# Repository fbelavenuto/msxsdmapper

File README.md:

# Projeto descontinuado
### Nova versão em https://github.com/fbelavenuto/msxsdmapperv2

## MSX SDMapper
Projeto SD Mapper/Megaram 512K para MSX

Copyright (c) 2014 Fabio Belavenuto. Licenced under CERN OHL v1.1

This documentation describes Open Hardware and is licensed under the CERN OHL v. 1.1.
You may redistribute and modify this documentation under the terms of the
[CERN OHL v.1.1](http://ohwr.org/cernohl). This documentation is distributed
WITHOUT ANY EXPRESS OR IMPLIED WARRANTY, INCLUDING OF MERCHANTABILITY,
SATISFACTORY QUALITY AND FITNESS FOR A PARTICULAR PURPOSE.
Please see the CERN OHL v.1.1 for applicable conditions

Este projeto implementa uma interface em forma de cartucho para adicionar um
dispositivo de armazenamento em massa utilizando até dois cartões SD (Secure
Digital) e uma Mapper ou Megaram de 512K para computadores da linha MSX.

O cartão SD pode ser padrão SD ou SDHC, o que limita o tamanho em no máximo
32GB.

Foi utilizado como sistema operacional o [Nextor](http://www.konamiman.com/msx/msx-e.html#nextor) sendo desenvolvido somente
o driver para se ter acesso aos dois cartões SD. O Nextor agora se tornou um projeto aberto em 2018.

O Nextor é uma evolução do MSX-DOS 2 tendo nativamente suporte a partições FAT16
de até 4GB, podendo ter 4 partições por cartão SD. Isso limita o máximo de uso do cartão SD em 16GB. É necessário 128KB de Mapper no mínimo para utilizar o Nextor com acesso à sub-diretórios, menos que 128K de mapper permite somente o uso do kernel do MSXDOS1 limitando em partições com FAT12 e máximo de 16MB por partição.

Uma chave seleciona entre os modos Mapper ou Megaram. A Megaram é um projeto do Ademir Carchano e permite executar ROMs de jogos/programas de cartuchos Megarom.

A função Mapper/Megaram pode ser desativada por uma outra chave e é útil no caso de usar a interface em um MSX que já tenha Mapper e não quiser usar a Megaram.

Foi criado um utilitário chamado "sdmupd.com" para poder atualizar a flash pelo próprio MSX.

Para compilar o driver e o utilitário sdmupd.com utilize o montador do próprio criador do Nextor [Nestor80](https://github.com/Konamiman/Nestor80) e para compilar o código do CPLD utilize o [Xilinx ISE Webpack](https://www.xilinx.com/support/download/index.html/content/xilinx/en/downloadNav/vivado-design-tools/archive-ise.html).

Agradecimentos ao Ademir Carchano pela invenção da Megaram, ao Luciano Sturaro pelo roteamento da placa e a comunidade MSXBR-L pelo apoio e incentivo.

#### Detalhes técnicos:

  - O código do CPLD implementa toda a lógica necessária, implementando um expansor
    de slots padrão, uma porta SPI modo 0, o controle da MegaROM padrão ASCII16
    utilizada pelo Nextor e o controle da Mapper ou Megaram de 512K.
  - Ao ativar a mapper/megaram, a interface ativa o expansor de slots, e com isso a
    interface funciona somente em slots não-expandidos. Porém, se desativar a
    mapper/megaram, o expansor de slots é desativado, permitindo utilizar o
    dispositivo de armazenamento em massa em slots expandidos.
  - A porta SPI implementada utiliza mapa de memória de $4000 a $48FF, sendo o 
    chaveamento entre ROM e SPI configurado pela escrita no endereço $6001.
  - Foi previsto a atualização da memória flash por software. Para isto foi
    implementado a porta 0x5F que controla a ativação ou não da gravação da flash.
    O bit 7 controla a permissão de gravação e os bits 2, 1 e 0 controlam a paginação
    de 16KB. Ao ativar o bit 7 a flash é mapeada em qualquer página (repete o mesmo
    espaço de 16K nas 4 páginas) e os bits 2, 1 e 0 controlam qual das 8 páginas da
    flash será mapeada. O sinal /WR da flash só é gerado quando o bit 7 está ativo.
    O utilitário sdmupd.com utiliza esta porta para poder atualizar a flash pelo
    próprio MSX.

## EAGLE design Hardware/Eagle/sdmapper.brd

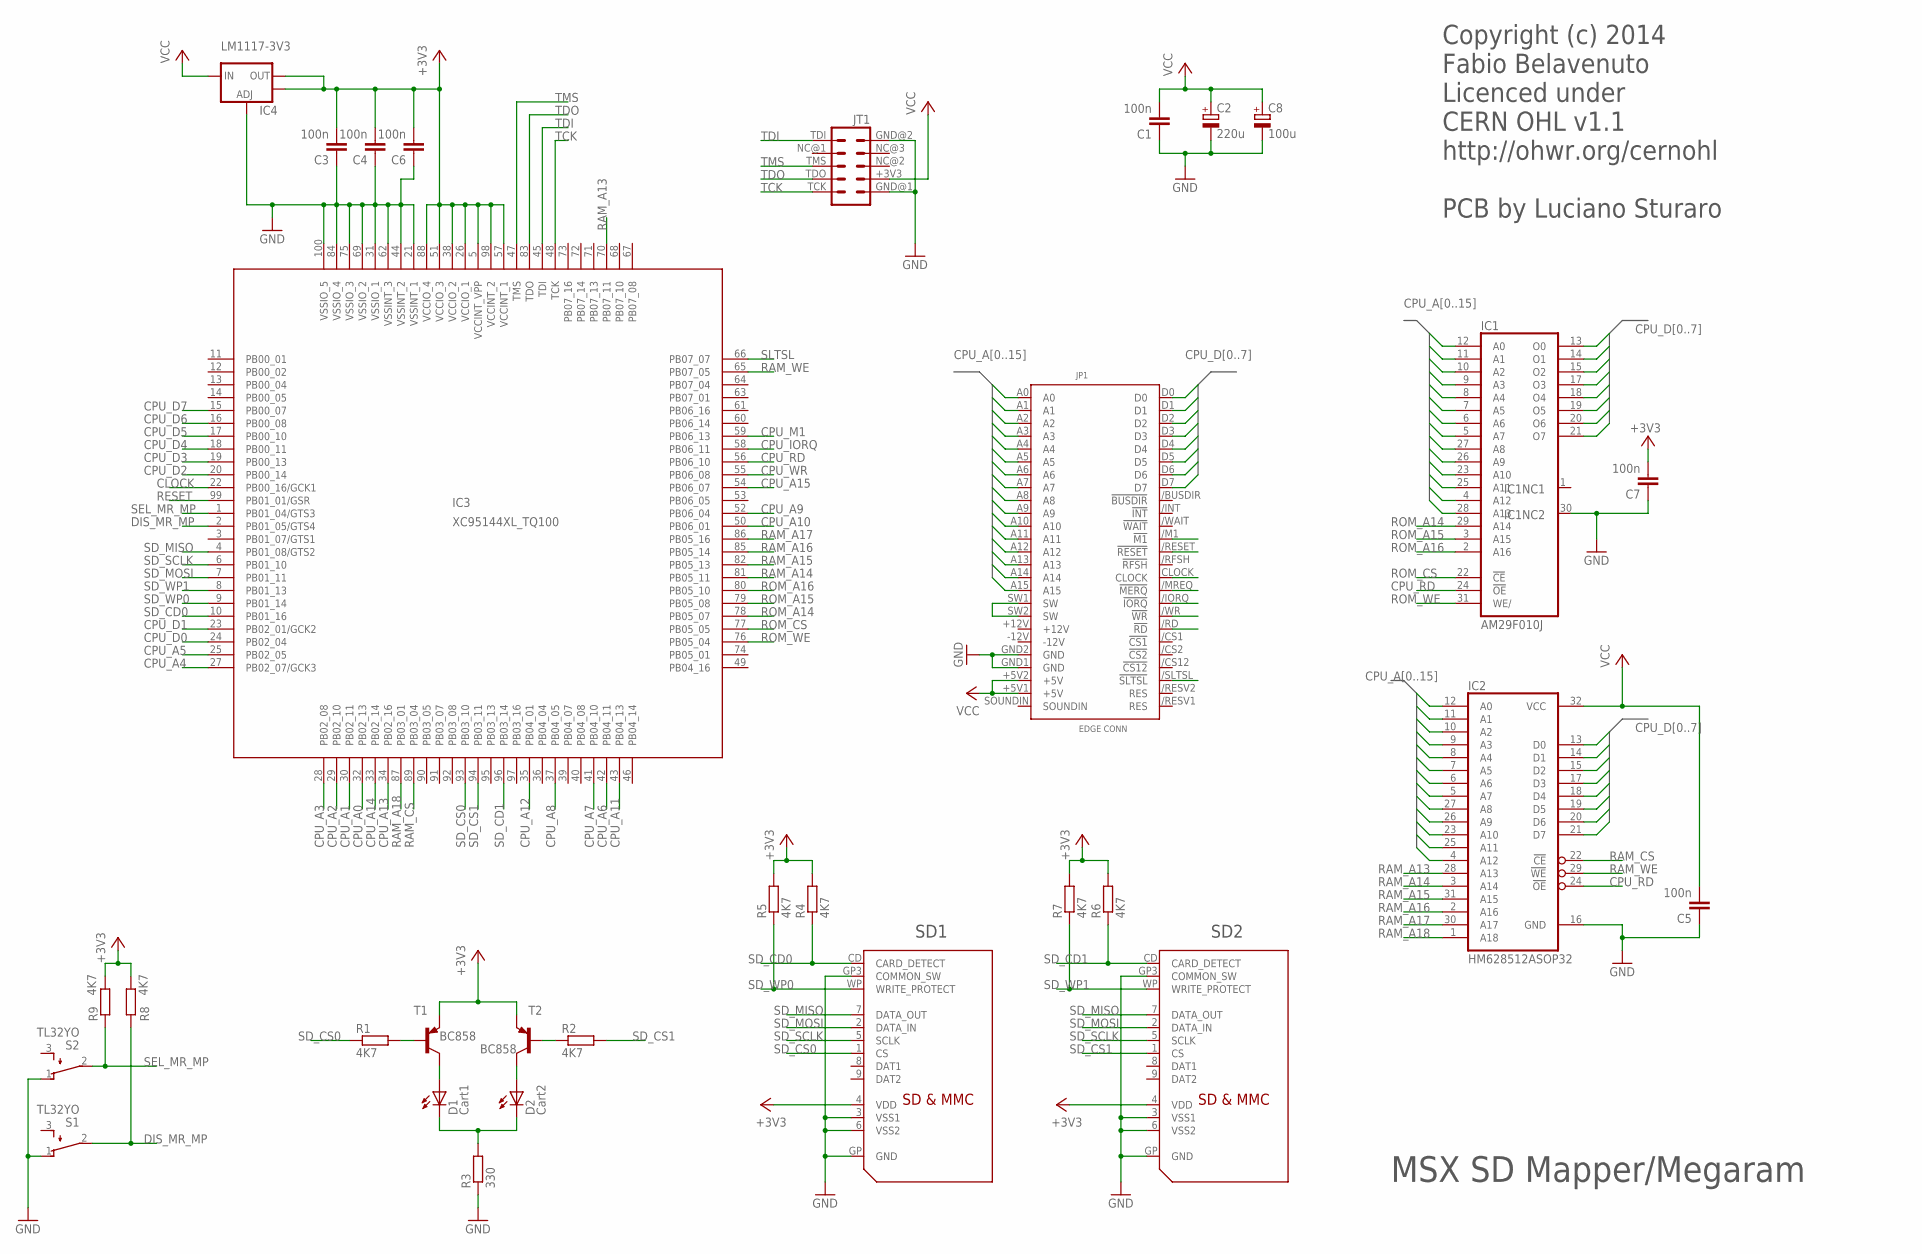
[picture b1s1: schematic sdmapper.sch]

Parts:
C1, C3, C4, C5: 100n; C0805
C2: 220u; E3,5-8
C6, C7: 100n; C1206
C8: 100u; PANASONIC_C
D1: Cart1; LED3MM
D2: Cart2; LED3MM
IC1: AM29F010J; PLCC32R
IC2: HM628512ASOP32; SOP32
IC3: XC95144XL_TQ100; XC-TQ100
IC4: LM1117-3V3; SOT223
JP1: MSXCART1; MSXCART
JT1: JTAG1B; SMD5X2
R1, R2, R4, R5, R6, R7, R8, R9: 4K7; R0805
R3: 330; R0805
S1, S2: TL32YO; TL3XYO
SD1, SD2: SDMMC06132; 06132
T1, T2: BC858; SOT23-BEC

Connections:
+3V3: C3.2, C4.2, C6.2, C7.2, IC3.5 (VCCINT_VPP), IC3.26 (VCCIO_1), IC3.38 (VCCIO_2), IC3.51 (VCCIO_3), IC3.57 (VCCINT_1), IC3.88 (VCCIO_4), IC3.98 (VCCINT_2), IC4.2 (OUT), IC4.4 (OUT), R4.2, R5.2, R6.2, R7.2, R8.2, R9.2, SD1.4 (VDD), SD2.4 (VDD), T1.E, T2.E
CLOCK: IC3.22 (PB00_16/GCK1), JP1.CLOCK
CPU_A0: IC1.12 (A0), IC2.12 (A0), IC3.32 (PB02_13), JP1.A0
CPU_A1: IC1.11 (A1), IC2.11 (A1), IC3.30 (PB02_11), JP1.A1
CPU_A2: IC1.10 (A2), IC2.10 (A2), IC3.29 (PB02_10), JP1.A2
CPU_A3: IC1.9 (A3), IC2.9 (A3), IC3.28 (PB02_08), JP1.A3
CPU_A4: IC1.8 (A4), IC2.8 (A4), IC3.27 (PB02_07/GCK3), JP1.A4
CPU_A5: IC1.7 (A5), IC2.7 (A5), IC3.25 (PB02_05), JP1.A5
CPU_A6: IC1.6 (A6), IC2.6 (A6), IC3.42 (PB04_11), JP1.A6
CPU_A7: IC1.5 (A7), IC2.5 (A7), IC3.41 (PB04_10), JP1.A7
CPU_A8: IC1.27 (A8), IC2.27 (A8), IC3.37 (PB04_05), JP1.A8
CPU_A9: IC1.26 (A9), IC2.26 (A9), IC3.52 (PB06_04), JP1.A9
CPU_A10: IC1.23 (A10), IC2.23 (A10), IC3.50 (PB06_01), JP1.A10
CPU_A11: IC1.25 (A11), IC2.25 (A11), IC3.43 (PB04_13), JP1.A11
CPU_A12: IC1.4 (A12), IC2.4 (A12), IC3.35 (PB04_01), JP1.A12
CPU_A13: IC1.28 (A13), IC3.34 (PB02_16), JP1.A13
CPU_A14: IC3.33 (PB02_14), JP1.A14
CPU_A15: IC3.54 (PB06_07), JP1.A15
CPU_D0: IC1.13 (O0), IC2.13 (D0), IC3.24 (PB02_04), JP1.D0
CPU_D1: IC1.14 (O1), IC2.14 (D1), IC3.23 (PB02_01/GCK2), JP1.D1
CPU_D2: IC1.15 (O2), IC2.15 (D2), IC3.20 (PB00_14), JP1.D2
CPU_D3: IC1.17 (O3), IC2.17 (D3), IC3.19 (PB00_13), JP1.D3
CPU_D4: IC1.18 (O4), IC2.18 (D4), IC3.18 (PB00_11), JP1.D4
CPU_D5: IC1.19 (O5), IC2.19 (D5), IC3.17 (PB00_10), JP1.D5
CPU_D6: IC1.20 (O6), IC2.20 (D6), IC3.16 (PB00_08), JP1.D6
CPU_D7: IC1.21 (O7), IC2.21 (D7), IC3.15 (PB00_07), JP1.D7
CPU_IORQ: IC3.58 (PB06_11), JP1./IORQ (!IORQ)
CPU_M1: IC3.59 (PB06_13), JP1./M1 (!M1)
CPU_MREQ: JP1./MREQ (!MERQ)
CPU_RD: IC1.24 (!OE), IC2.24 (!OE), IC3.56 (PB06_10), JP1./RD (!RD)
CPU_WR: IC3.55 (PB06_08), JP1./WR (!WR)
DIS_MR_MP: IC3.2 (PB01_05/GTS4), R8.1, S1.2
GND: C1.1, C2.-, C3.1, C4.1, C5.1, C6.1, C7.1, C8.-, IC1.16 (GND), IC1.30 (NC), IC2.16 (GND), IC3.21 (VSSINT_1), IC3.31 (VSSIO_1), IC3.44 (VSSINT_2), IC3.62 (VSSINT_3), IC3.69 (VSSIO_2), IC3.75 (VSSIO_3), IC3.84 (VSSIO_4), IC3.100 (VSSIO_5), IC4.1 (ADJ), JP1.GND1 (GND), JP1.GND2 (GND), JT1.GND@1 (TDI), JT1.GND@2 (TCK), R3.1, S1.1 (O), S2.1 (O), SD1.3 (VSS1), SD1.6 (VSS2), SD1.GP (GND), SD1.GP3 (COMMON_SW), SD2.3 (VSS1), SD2.6 (VSS2), SD2.GP (GND), SD2.GP3 (COMMON_SW)
unnamed: JP1.SW1 (SW), JP1.SW2 (SW)
unnamed: R1.2, T1.B
unnamed: R2.1, T2.B
unnamed: D1.K (C), D2.K (C), R3.2
unnamed: D1.A, T1.C
unnamed: D2.A, T2.C
RAM_A13: IC2.28 (A13), IC3.70 (PB07_11)
RAM_A14: IC2.3 (A14), IC3.81 (PB05_11)
RAM_A15: IC2.31 (A15), IC3.82 (PB05_13)
RAM_A16: IC2.2 (A16), IC3.85 (PB05_14)
RAM_A17: IC2.30 (A17), IC3.86 (PB05_16)
RAM_A18: IC2.1 (A18), IC3.87 (PB03_01)
RAM_CS: IC2.22 (!CE), IC3.89 (PB03_04)
RAM_WE: IC2.29 (!WE), IC3.65 (PB07_05)
RESET: IC3.99 (PB01_01/GSR), JP1./RESET (!RESET)
ROM_A14: IC1.29 (A14), IC3.78 (PB05_07)
ROM_A15: IC1.3 (A15), IC3.79 (PB05_08)
ROM_A16: IC1.2 (A16), IC3.80 (PB05_10)
ROM_CS: IC1.22 (!CE), IC3.77 (PB05_05)
ROM_WE: IC1.31 (WE/), IC3.76 (PB05_04)
SD_CD0: IC3.10 (PB01_16), R4.1, SD1.CD (CARD_DETECT)
SD_CD1: IC3.96 (PB03_14), R6.1, SD2.CD (CARD_DETECT)
SD_CS0: IC3.93 (PB03_10), R1.1, SD1.1 (CS)
SD_CS1: IC3.94 (PB03_11), R2.2, SD2.1 (CS)
SD_MISO: IC3.4 (PB01_08/GTS2), SD1.7 (DATA_OUT), SD2.7 (DATA_OUT)
SD_MOSI: IC3.7 (PB01_11), SD1.2 (DATA_IN), SD2.2 (DATA_IN)
SD_SCLK: IC3.6 (PB01_10), SD1.5 (SCLK), SD2.5 (SCLK)
SD_WP0: IC3.9 (PB01_14), R5.1, SD1.WP (WRITE_PROTECT)
SD_WP1: IC3.8 (PB01_13), R7.1, SD2.WP (WRITE_PROTECT)
SEL_MR_MP: IC3.1 (PB01_04/GTS3), R9.1, S2.2
SLTSL: IC3.66 (PB07_07), JP1./SLTSL (!SLTSL)
TCK: IC3.48 (TCK), JT1.TCK (GND)
TDI: IC3.45 (TDI), JT1.TDI (GND)
TDO: IC3.83 (TDO), JT1.TDO (NC)
TMS: IC3.47 (TMS), JT1.TMS (NC)
VCC: C1.2, C2.+, C5.2, C8.+, IC1.32 (VCC), IC2.32 (VCC), IC4.3 (IN), JP1.+5V1 (+5V), JP1.+5V2 (+5V), JT1.+3V3 (NC)

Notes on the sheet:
MSX SD Mapper/Megaram
Copyright (c) 2014 Fabio Belavenuto Licenced under CERN OHL v1.1 http://ohwr.org/cernohl PCB by Luciano Sturaro
SD1
SD2

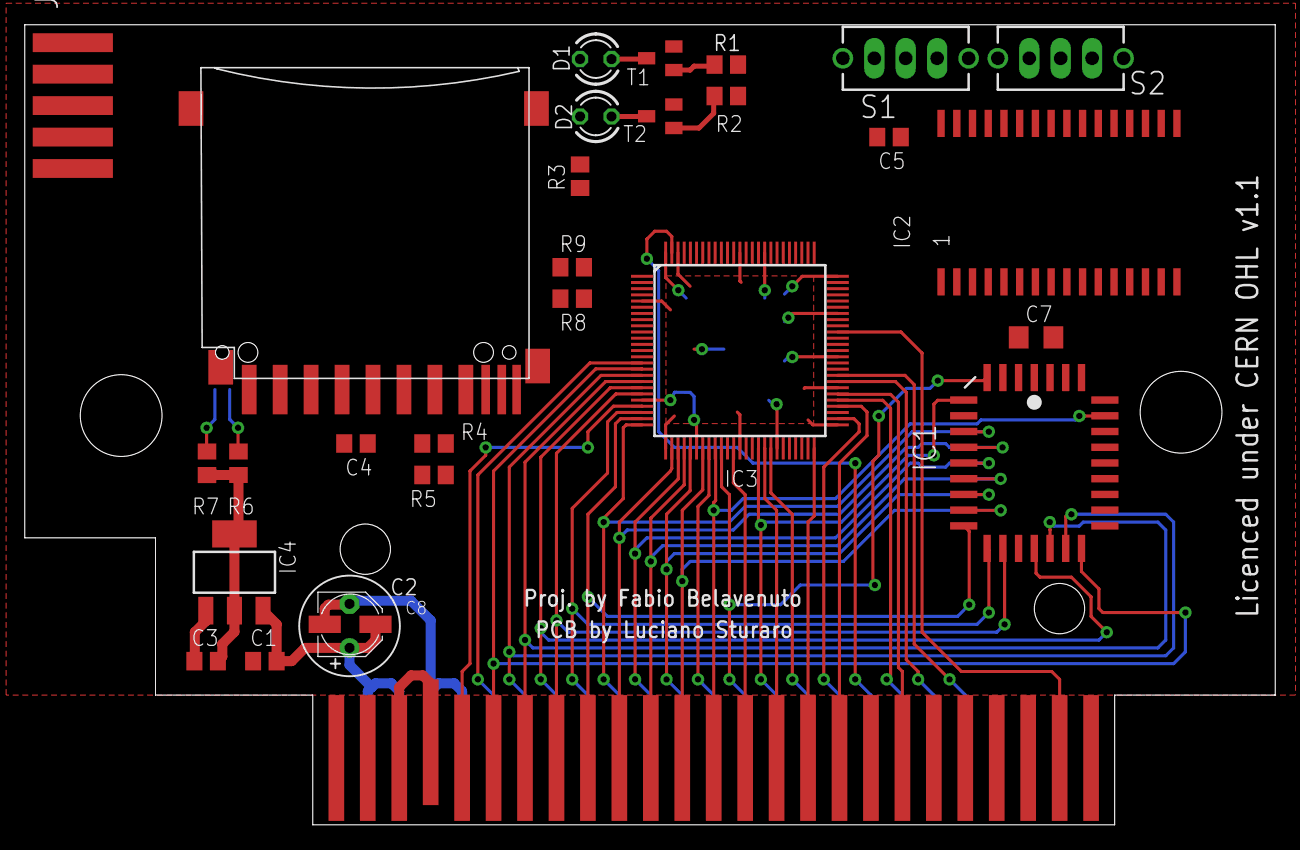
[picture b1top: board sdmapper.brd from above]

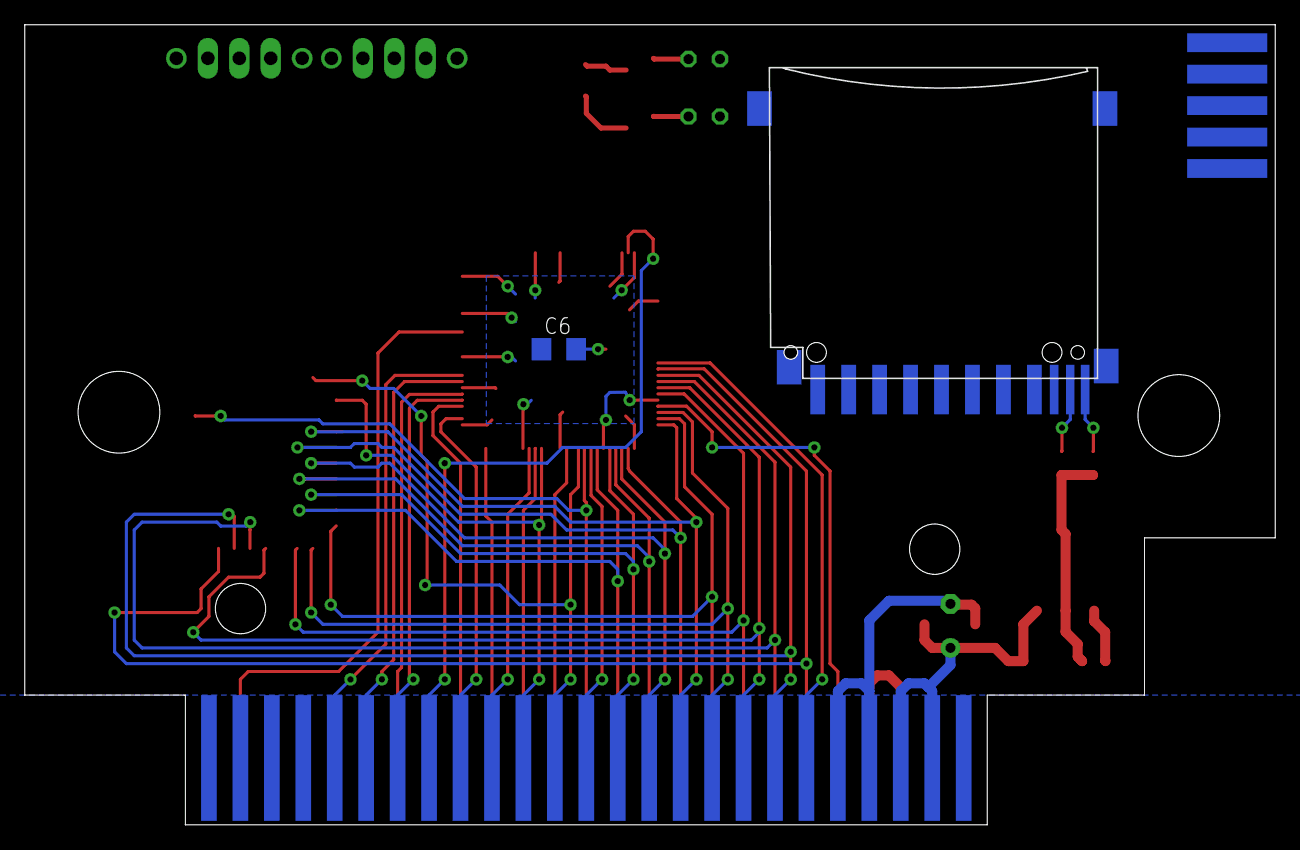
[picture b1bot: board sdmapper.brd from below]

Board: 2 copper layers, 101.0 x 64.6 mm, 31 parts (2 on the bottom side), 68 nets.

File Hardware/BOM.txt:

Qty Value           Device               Package     Parts                          Description
1   AM29F010J       AM29F010J            PLCC32R     IC1                            1-Megabit FLASH MEMORY
1   HM628512A       HM628512ASOP32       SOP32       IC2                            4M SRAM 512kword x 8bit
1   XC95144XL       XC95144XL_TQ100      XC-TQ100    IC3                            xc95144xl_tq100
1   LM1117-3V3      V_REG_LM1117SOT223   SOT223      IC4                            Voltage Regulator LM1117
2   SDMMC06132      SDMMC06132           06132       SD1, SD2                       SD MMC Card holder
2   TL32YO          TL32YO               TL3XYO      S1, S2                         TINY SWITCH ON - MOM
4   100n            C-EUC0805            C0805       C1, C3, C4, C5                 CAPACITOR, European symbol
2   100n            C-EUC1206            C1206       C6, C7                         CAPACITOR, European symbol
1   100u            CPOL-EUC             PANASONIC_C C8                             POLARIZED CAPACITOR, European symbol
1   220u            CPOL-EUE3.5-8        E3,5-8      C2                             POLARIZED CAPACITOR, European symbol
1   330             R-EU_R0805           R0805       R3                             RESISTOR, European symbol
8   4K7             R-EU_R0805           R0805       R1, R2, R4, R5, R6, R7, R8, R9 RESISTOR, European symbol
2   BC858           BC858A-PNP-SOT23-BEC SOT23-BEC   T1, T2                         PNP Transistror
1   Cart1           LED3MM               LED3MM      D1                             LED
1   Cart2           LED3MM               LED3MM      D2                             LED

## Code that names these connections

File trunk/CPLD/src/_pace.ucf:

#PACE: Start of Constraints generated by PACE

#PACE: Start of PACE I/O Pin Assignments
NET "clock"  LOC = "P22"  ; 
NET "reset_n"  LOC = "P99"  ; 
NET "dis_mapper"  LOC = "p79"  ; 
NET "mr_mp"  LOC = "P10";
NET "wr_n"  LOC = "p74"  ; 
NET "rd_n"  LOC = "p72"  ; 
NET "sltsl_n"  LOC = "p78"  ; 
NET "iorq_n"  LOC = "p73"  ; 
NET "m1_n"  LOC = "p77"  ; 
NET "addr_bus<15>"  LOC = "p71"  ; 
NET "addr_bus<14>"  LOC = "p40"  ; 
NET "addr_bus<13>"  LOC = "p63"  ; 
NET "addr_bus<12>"  LOC = "p64"  ; 
NET "addr_bus<11>"  LOC = "p68"  ; 
NET "addr_bus<10>"  LOC = "p76"  ; 
NET "addr_bus<9>"  LOC = "p70"  ; 
NET "addr_bus<8>"  LOC = "p65"  ; 
NET "addr_bus<7>"  LOC = "p66"  ; 
NET "addr_bus<6>"  LOC = "p67"  ; 
NET "addr_bus<5>"  LOC = "p56"  ; 
NET "addr_bus<4>"  LOC = "p43"  ; 
NET "addr_bus<3>"  LOC = "p58"  ; 
NET "addr_bus<2>"  LOC = "p59"  ; 
NET "addr_bus<1>"  LOC = "p60"  ; 
NET "addr_bus<0>"  LOC = "p61"  ; 
NET "data_bus<7>"  LOC = "p50"  ; 
NET "data_bus<6>"  LOC = "p49"  ; 
NET "data_bus<5>"  LOC = "p52"  ; 
NET "data_bus<4>"  LOC = "p53"  ; 
NET "data_bus<3>"  LOC = "p46"  ; 
NET "data_bus<2>"  LOC = "p42"  ; 
NET "data_bus<1>"  LOC = "p54"  ; 
NET "data_bus<0>"  LOC = "p55"  ; 
NET "ram_a<18>"  LOC = "p41"  ; 
NET "ram_a<17>"  LOC = "p90"  ; 
NET "ram_a<16>"  LOC = "p39"  ; 
NET "ram_a<15>"  LOC = "p82"  ; 
NET "ram_a<14>"  LOC = "p36"  ; 
NET "ram_a<13>"  LOC = "81"  ; 
NET "ram_cs"  LOC = "p92"  ; 
NET "ram_we"  LOC = "80"  ; 
NET "rom_a<16>"  LOC = "p95"  ; 
NET "rom_a<15>"  LOC = "p96"  ; 
NET "rom_a<14>"  LOC = "p94"  ; 
NET "rom_cs"  LOC = "p91"  ; 
NET "rom_we"  LOC = "p97"  ; 
NET "sd_cs<1>"  LOC = "p28"  ; 
NET "sd_cs<0>"  LOC = "p29"  ; 
NET "sd_inserted<1>"  LOC = "p25"  ;
NET "sd_inserted<0>"  LOC = "p34"  ; 
NET "sd_miso"  LOC = "p35"  ; 
NET "sd_mosi"  LOC = "p32"  ; 
NET "sd_sclk"  LOC = "p33"  ; 
NET "sd_writeprot<0>"  LOC = "p37"  ; 
NET "sd_writeprot<1>"  LOC = "P30"  ;

#PACE: Start of PACE Area Constraints

#PACE: Start of PACE Prohibit Constraints

#PACE: End of Constraints generated by PACE

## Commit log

2014-01-10 Initial directory structure.
2014-01-10 upload inicial
2014-01-10 Updater: adicionado reconhecimento de mais chips flash
2014-01-10 Terminado layout da placa Atualizado esquema.pdf Atualizado pinout no projeto do ISE
2014-01-10 Corrigido footprint da SRAM Retirado LEDs comuns e trocado por LED bi-color Layout da placa foi otimizada
2014-01-11 Otimização na placa utilitário de gravação reconhece mais marcas/modelos de flash adicionado binários do driver e atualizador
2014-07-31 Modificado porta SPI no CPLD para trabalhar assincronicamente. Adicionado oscilador de 25MHz na placa. Modificado porta de controle do updater. Estudando desenvolvimento do driver para Symbos
2014-07-31 Resolvendo conflitos
2014-09-12 CPLD com pinout do produto final. Adicionado versao 2.0.3 do Nextor. Mudado nome da ROM de NEXTOR.ROM para SDMAPPER.ROM Adicionado na inicializacao do driver a chamada a funcao INITXT para exibir men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
2014-09-12 Adicionado Driver.lst Retirado arquivos temporarios do CPLD
2014-10-16 Adicionado gerbers da placa roteada pelo Sturaro Adicionado versão em PDF e postscript da placa para fabricação caseira Adicionado lista de materiais Adicionado etiquetas em alta resolução para a cai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
2014-10-16 Created wiki page through web user interface.
2014-10-16 Edited wiki page Informacoes through web user interface.
2014-10-21 Updater: Corrigido ID da flash AMD
2014-10-22 Edited wiki page LinksEbay through web user interface.
2014-11-04 Atualizado versão no Nextor para 2.0.4 Realocado alguns diretórios para acomodar versões diferentes do Nextor
2014-12-20 Adicionado arquivos de gravação do CPLD nos formatos STAPL e SVF. Adicionado versão do driver em binário com patch para funcionar nas máquinas CIEL 2+. Corrigido BUG na placa onde o pino 1 da flash f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
2015-03-18 Migrating wiki contents from Google Code
2015-03-18 Atualizado versao do Nextor para 2.1 alpha 2
2015-03-21 Acertado nome da pasta dos arquivos no Nextor 2.1 alpha 2
2016-10-19 Corrigido bug na captura das portas da Mapper, agora interface funciona nos micros Expert Plus e DD Plus
2016-10-31 Added updated binaries, for programming.
2017-04-15 Delay fixes in SD recognize.
2017-05-11 Added JTAG documentation
2017-05-24 New driver with FRS enhancements.
2017-05-24 Driver enhancements, version 1.0.6
2017-06-22 Added new label
2017-09-27 cosmetics
2017-11-11 Bugged driver (replaced with 1.0.4 version)
2017-11-13 Added support to STM29F010B in the updater.
2018-10-04 Testing fixed Nextor FAT16 recognize
2018-10-06 New nextor not working!
2019-05-07 Updated to Nextor 2.1.0 Beta 2
2019-05-07 Versao para Ravazzi
2023-11-09 Using docker to build ROM
2023-11-09 Try fixing driver with @Emily82 discover
2023-12-03 Fixed write corrupt bug
2023-12-04 Testing driver 1.0.4 with N80 compiler
2023-12-04 Testing with n80
2023-12-04 Fix cp a, n -> cp a, cp n
2023-12-05 Driver 1.0.4 working
2023-12-05 Fixed corruption bug
2023-12-06 Renaming to uppercase
2023-12-11 Make sdmapper.jed via ISE 14.7 docker image
2023-12-11 Organizing documentation and files. Using Docker to compile the CPLD bitstream Testing Github Actions
2023-12-11 Removing github actions
2024-05-03 Little fixes

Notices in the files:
parts and their libraries:
SparkFun-PowerIC: Licensing: CC v3.0 Share-Alike You are welcome to use this library for commercial purposes.
